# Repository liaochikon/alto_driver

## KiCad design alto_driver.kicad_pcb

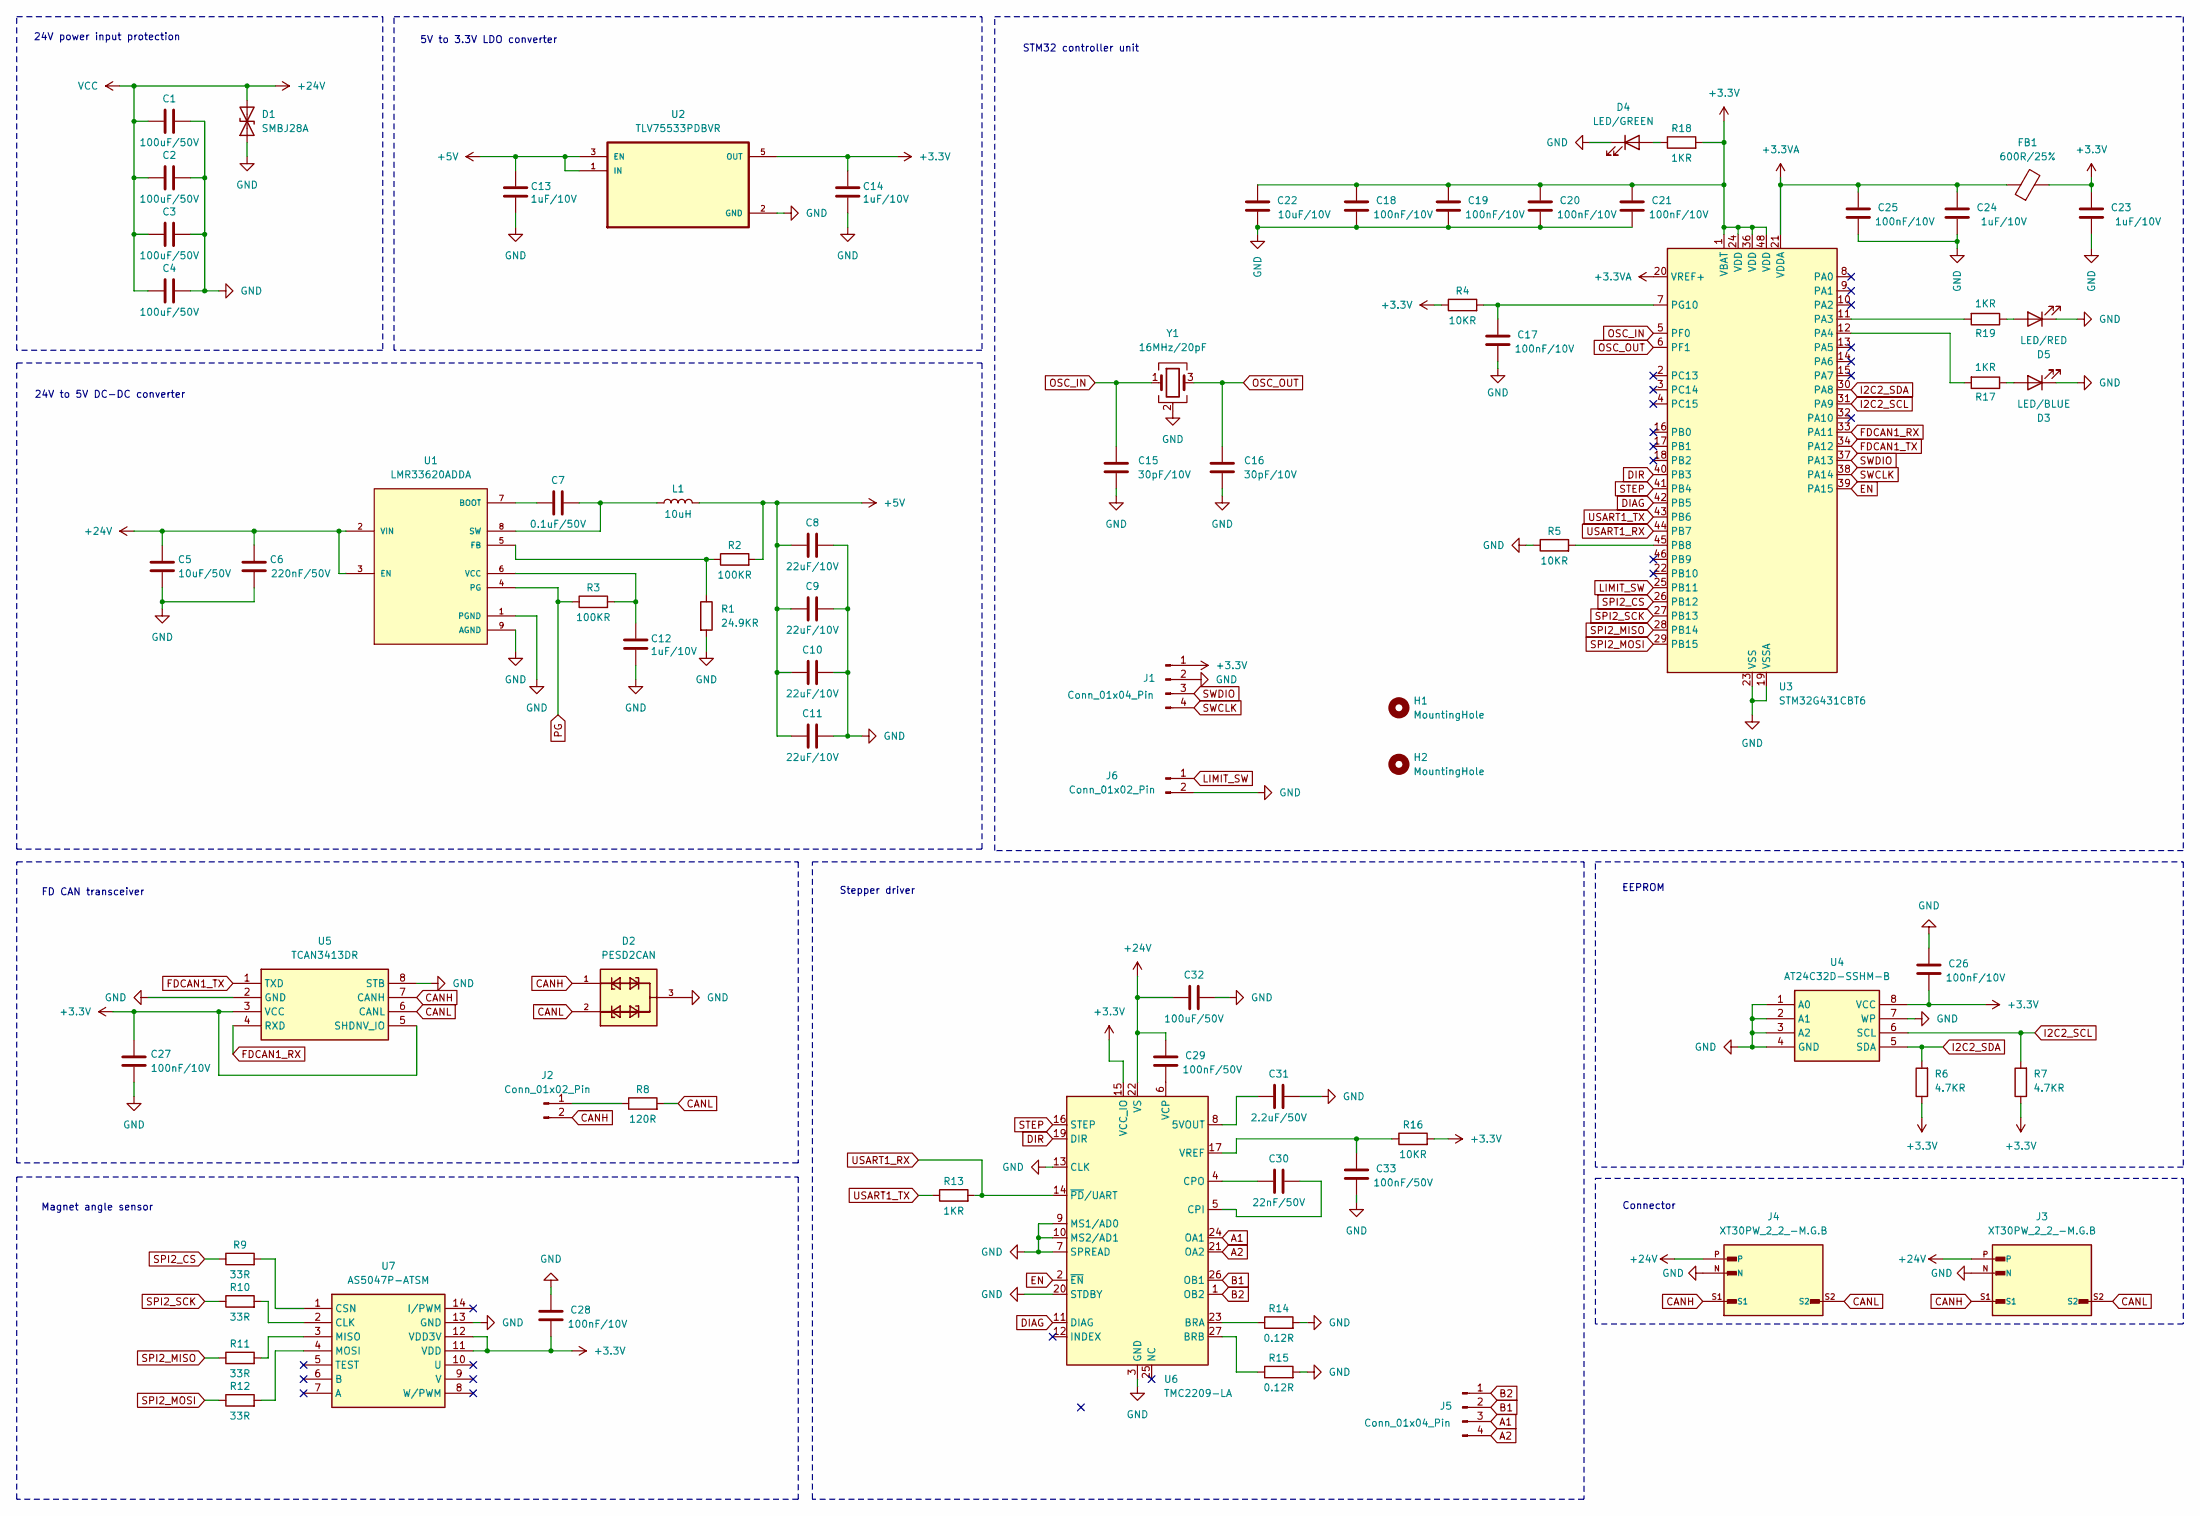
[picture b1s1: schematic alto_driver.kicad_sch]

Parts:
C1, C2, C3, C4, C32: 100uF/50V; C_1210_3225Metric
C5: 10uF/50V; C_0603_1608Metric
C6: 220nF/50V; C_0603_1608Metric
C7: 0.1uF/50V; C_0603_1608Metric
C8, C9, C10, C11: 22uF/10V; C_0603_1608Metric
C12, C13, C14, C23, C24: 1uF/10V; C_0603_1608Metric
C15, C16: 30pF/10V; C_0603_1608Metric
C17, C18, C19, C20, C21, C25, C26, C27, C28: 100nF/10V; C_0603_1608Metric
C22: 10uF/10V; C_0603_1608Metric
C29, C33: 100nF/50V; C_0603_1608Metric
C30: 22nF/50V; C_0603_1608Metric
C31: 2.2uF/50V; C_0603_1608Metric
D1: SMBJ28A; D_SMB
D2: PESD2CAN; SOT95P230X110-3N
D3: LED/BLUE; LED_0603_1608Metric
D4: LED/GREEN; LED_0603_1608Metric
D5: LED/RED; LED_0603_1608Metric
FB1: 600R/25%; L_0603_1608Metric
H1, H2: MountingHole; MountingHole_3.2mm_M3
J1: Conn_01x04_Pin; PinHeader_1x04_P2.54mm_Vertical
J2: Conn_01x02_Pin; PinHeader_1x02_P2.54mm_Vertical
J3, J4: XT30PW_2_2_-M.G.B; AMASS_XT30PW_2_2_-M.G.B; PARTREV NA
J5: Conn_01x04_Pin; JST_XH_S4B-XH-A_1x04_P2.50mm_Horizontal
J6: Conn_01x02_Pin; JST_XH_S2B-XH-A_1x02_P2.50mm_Horizontal
L1: 10uH; L_Chilisin_BWVS00505030
R1: 24.9KR; R_0603_1608Metric
R2, R3: 100KR; R_0603_1608Metric
R4, R5, R16: 10KR; R_0603_1608Metric
R6, R7: 4.7KR; R_0603_1608Metric
R8: 120R; R_0603_1608Metric
R9, R10, R11, R12: 33R; R_0603_1608Metric
R13, R17, R18, R19: 1KR; R_0603_1608Metric
R14, R15: 0.12R; R_1206_3216Metric
U1: LMR33620ADDA; CONV_LMR33620ADDA; PARTREV C
U2: TLV75533PDBVR; SOT95P280X145-5N
U3: STM32G431CBT6; LQFP-48_7x7mm_P0.5mm
U4: AT24C32D-SSHM-B; SOIC127P600X175-8N; Manufacturer_Part_Number AT24C32D-SSHM-B; Mouser Part Number 556-AT24C32D-SSHM-B
U5: TCAN3413DR; SOIC127P600X175-8N; Manufacturer_Part_Number TCAN3413DR; Mouser Part Number 595-TCAN3413DR
U6: TMC2209-LA; QFN50P500X500X90-29N
U7: AS5047P-ATSM; SOP65P640X120-14N; Manufacturer_Part_Number AS5047P-ATSM; Mouser Part Number 985-AS5047P-ATSM
Y1: 16MHz/20pF; Crystal_SMD_3225-4Pin_3.2x2.5mm

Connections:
+3.3V: C14.2, C18.1, C19.1, C20.1, C21.1, C22.1, C23.1, C26.2, C27.2, C28.2, FB1.2, J1.1, R4.1, R6.1, R7.1, R16.2, R18.2, U2.5 (OUT), U3.1 (VBAT), U3.24 (VDD), U3.36 (VDD), U3.48 (VDD), U4.8 (VCC), U5.3 (VCC), U5.5 (SHDNV_IO), U6.15 (VCC_IO), U7.11 (VDD), U7.12 (VDD3V)
+3.3VA: C24.1, C25.1, FB1.1, U3.20 (VREF+), U3.21 (VDDA)
+5V: C8.1, C9.1, C10.1, C11.1, C13.2, L1.2, R2.2, U2.1 (IN), U2.3 (EN)
+24V: C1.1, C2.1, C3.1, C4.1, C5.1, C6.1, C29.1, C32.1, D1.2 (A2), J3.P, J4.P, U1.2 (VIN), U1.3 (EN), U6.22 (VS), U6.28 (VS)
A1: J5.3, U6.24 (OA1)
A2: J5.4, U6.21 (OA2)
B1: J5.2, U6.26 (OB1)
B2: J5.1, U6.1 (OB2)
CANH: D2.1, J2.2, J3.S1, J4.S1, U5.7 (CANH)
CANL: D2.2, J3.S2, J4.S2, R8.2, U5.6 (CANL)
DIAG: U3.42 (PB5), U6.11 (DIAG)
DIR: U3.40 (PB3), U6.19 (DIR)
EN: U3.39 (PA15), U6.2 (~EN)
FDCAN1_RX: U3.33 (PA11), U5.4 (RXD)
FDCAN1_TX: U3.34 (PA12), U5.1 (TXD)
GND: C1.2, C2.2, C3.2, C4.2, C5.2, C6.2, C8.2, C9.2, C10.2, C11.2, C12.1, C13.1, C14.1, C15.2, C16.2, C17.2, C18.2, C19.2, C20.2, C21.2, C22.2, C23.2, C24.2, C25.2, C26.1, C27.1, C28.1, C31.2, C32.2, C33.2, D1.1 (A1), D2.3, D3.1 (K), D4.1 (K), D5.1 (K), J1.2, J3.N, J4.N, J6.2, R1.2, R5.1, R14.2, R15.2, U1.1 (PGND), U1.9 (AGND), U1.9_1 (AGND), U1.9_2 (AGND), U1.9_3 (AGND), U1.9_4 (AGND), U1.9_5 (AGND), U1.9_6 (AGND), U1.9_7 (AGND), U1.9_8 (AGND), U2.2 (GND), U3.19 (VSSA), U3.23 (VSS), U3.35 (VSS), U3.47 (VSS), U4.1 (A0), U4.2 (A1), U4.3 (A2), U4.4 (GND), U4.7 (WP), U5.2 (GND), U5.8 (STB), U6.3 (GND), U6.7 (SPREAD), U6.9 (MS1/AD0), U6.10 (MS2/AD1), U6.13 (CLK), U6.18 (GND), U6.20 (STDBY), U6.29 (GND), U7.13 (GND), Y1.2 (G), Y1.4 (G)
I2C2_SCL: R7.2, U3.31 (PA9), U4.6 (SCL)
I2C2_SDA: R6.2, U3.30 (PA8), U4.5 (SDA)
LIMIT_SW: J6.1, U3.25 (PB11)
unnamed: D3.2 (A), R17.1
unnamed: D4.2 (A), R18.1
unnamed: D5.2 (A), R19.1
unnamed: J2.1, R8.1
unnamed: C7.1, U1.7 (BOOT)
unnamed: R1.1, R2.1, U1.5 (FB)
unnamed: C7.2, L1.1, U1.8 (SW)
unnamed: C12.2, R3.2, U1.6 (VCC)
unnamed: R19.2, U3.11 (PA3)
unnamed: R17.2, U3.12 (PA4)
unnamed: R5.2, U3.45 (PB8)
unnamed: C17.1, R4.2, U3.7 (PG10)
unnamed: C31.1, U6.8 (5VOUT)
unnamed: R14.1, U6.23 (BRA)
unnamed: R15.1, U6.27 (BRB)
unnamed: C30.2, U6.5 (CPI)
unnamed: C30.1, U6.4 (CPO)
unnamed: C29.2, U6.6 (VCP)
unnamed: C33.1, R16.1, U6.17 (VREF)
unnamed: R10.2, U7.2 (CLK)
unnamed: R9.2, U7.1 (CSN)
unnamed: R11.2, U7.3 (MISO)
unnamed: R12.2, U7.4 (MOSI)
OSC_IN: C15.1, U3.5 (PF0), Y1.1
OSC_OUT: C16.1, U3.6 (PF1), Y1.3
PG: R3.1, U1.4 (PG)
SPI2_CS: R9.1, U3.26 (PB12)
SPI2_MISO: R11.1, U3.28 (PB14)
SPI2_MOSI: R12.1, U3.29 (PB15)
SPI2_SCK: R10.1, U3.27 (PB13)
STEP: U3.41 (PB4), U6.16 (STEP)
SWCLK: J1.4, U3.38 (PA14)
SWDIO: J1.3, U3.37 (PA13)
USART1_RX: R13.2, U3.44 (PB7), U6.14 (~PD/UART)
USART1_TX: R13.1, U3.43 (PB6)

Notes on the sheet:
Magnet angle sensor
24V to 5V DC-DC converter
Connector
5V to 3.3V LDO converter
EEPROM
Stepper driver
24V power input protection
FD CAN transceiver
STM32 controller unit

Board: 4 copper layers, 75 parts (12 on the bottom side), 54 nets, no tracks yet.

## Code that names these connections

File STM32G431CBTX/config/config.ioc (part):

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Mcu.Name=STM32G431C(6-8-B)Tx
Mcu.Package=LQFP48
Mcu.UserName=STM32G431CBTx
PA11.Mode=FDCAN_Activate
PA11.Signal=FDCAN1_RX
PA12.Mode=FDCAN_Activate
PA12.Signal=FDCAN1_TX
PA13.Mode=Serial_Wire
PA13.Signal=SYS_JTMS-SWDIO
PA14.Mode=Serial_Wire
PA14.Signal=SYS_JTCK-SWCLK
PA15.GPIOParameters=GPIO_Label
PA15.GPIO_Label=EN
PA15.Signal=GPIO_Output
PA3.GPIOParameters=GPIO_Label
PA3.GPIO_Label=RED_LED
PA3.Signal=GPIO_Output
PA4.GPIOParameters=GPIO_Label
PA4.GPIO_Label=BLUE_LED
PA4.Signal=GPIO_Output
PA8.Mode=I2C
PA8.Signal=I2C2_SDA
PA9.Mode=I2C
PA9.Signal=I2C2_SCL
PB11.GPIOParameters=GPIO_Label
PB11.GPIO_Label=LIMIT_SW
PB11.Signal=GPIO_Input
PB12.GPIOParameters=GPIO_Label
PB12.GPIO_Label=SPI2_CS
PB12.Signal=GPIO_Output
PB13.Mode=Full_Duplex_Master
PB13.Signal=SPI2_SCK
PB14.Mode=Full_Duplex_Master
PB14.Signal=SPI2_MISO
PB15.Mode=Full_Duplex_Master
PB15.Signal=SPI2_MOSI
PB3.GPIOParameters=GPIO_Label
PB3.GPIO_Label=DIR
PB3.Signal=GPIO_Output
PB4.GPIOParameters=GPIO_Label
PB4.GPIO_Label=STEP
PB4.Signal=GPIO_Output
PB5.GPIOParameters=GPIO_Label
PB5.GPIO_Label=DIAG
PB5.Signal=GPIO_Input
PB6.Mode=Asynchronous
PB6.Signal=USART1_TX
PB7.Mode=Asynchronous
PB7.Signal=USART1_RX
PF0-OSC_IN.Mode=HSE-External-Oscillator
PF0-OSC_IN.Signal=RCC_OSC_IN
PF1-OSC_OUT.Mode=HSE-External-Oscillator
PF1-OSC_OUT.Signal=RCC_OSC_OUT
RCC.HSE_VALUE=16000000
RCC.SYSCLKFreq_VALUE=170000000
RCC.SYSCLKSource=RCC_SYSCLKSOURCE_PLLCLK
board=custom

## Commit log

2026-03-09 0309
2026-03-14 0314
2026-03-20 0321
